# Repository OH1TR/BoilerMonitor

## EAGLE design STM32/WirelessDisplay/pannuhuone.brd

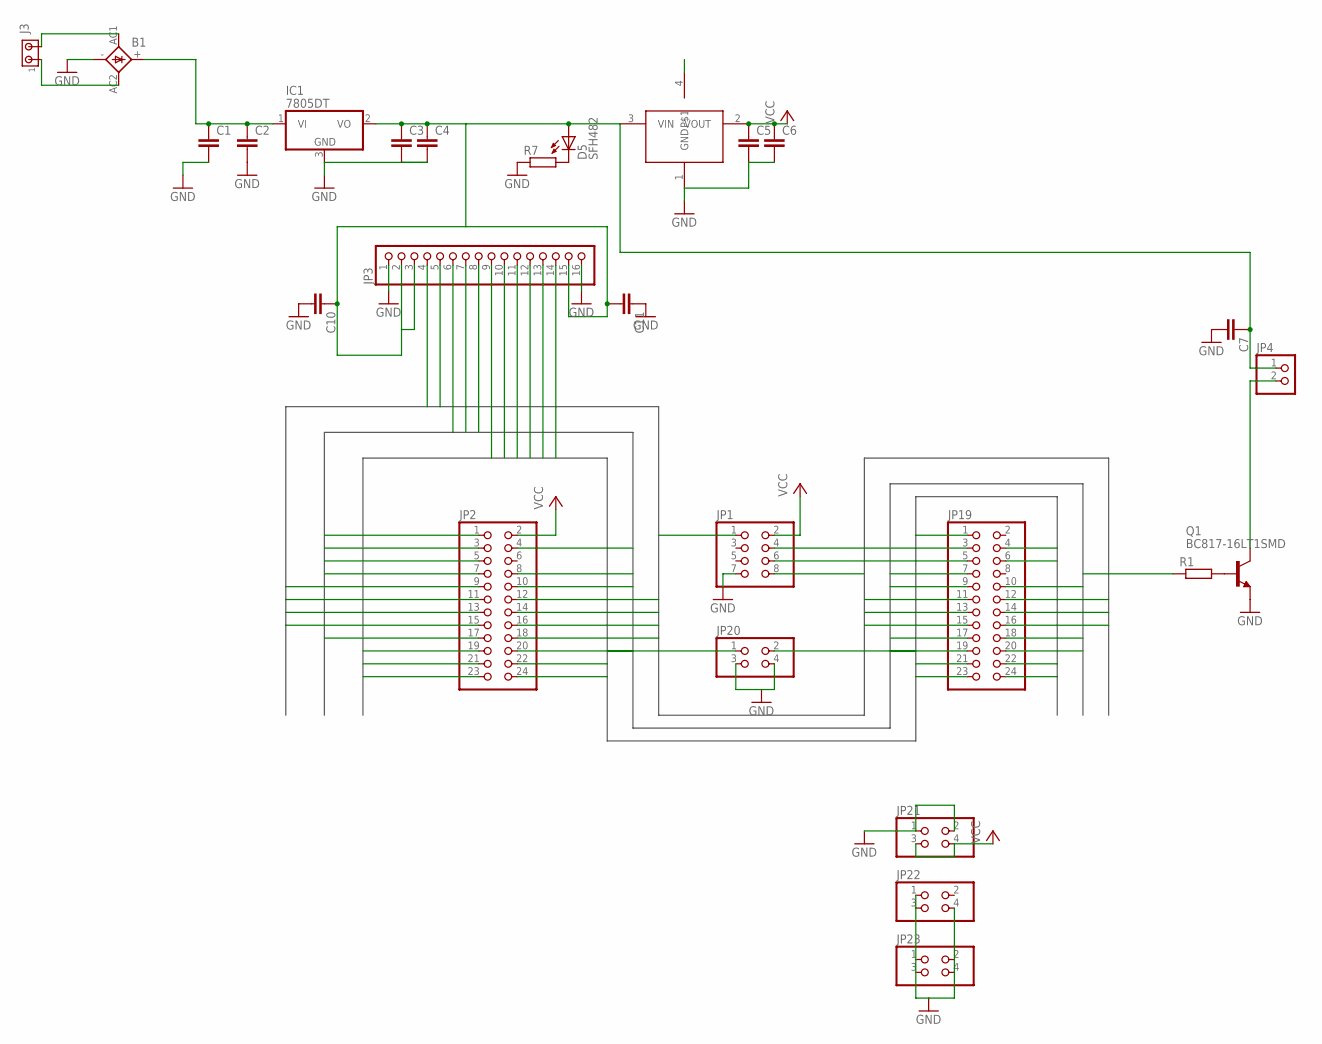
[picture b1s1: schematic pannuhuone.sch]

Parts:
B1: 2KBB-R
C1: C-EU025-050X050; C025-050X050
C2, C3, C4, C5, C6, C7, C10, C11: C-EUC1206; C1206
D5: SFH482
IC1: 7805DT; TO252
J3: MTA02-156; 1X2MTA
JP1: PINHD-2X4; 2X04
JP2, JP19: PINHD-2X12; 2X12
JP3: PINHD-1X16; 1X16
JP4: PINHD-1X2; 1X02
JP20, JP21, JP22, JP23: PINHD-2X2; 2X02
Q1: BC817-16LT1SMD; SOT23-BEC
R1, R7: R-EU_R1206; R1206
U$2: LD1117; SOT223

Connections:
GND: B1.-, C1.2, C2.2, C3.2, C4.2, C5.2, C6.2, C7.2, C10.2, C11.1, IC1.3 (GND), JP1.7, JP3.1, JP3.16, JP20.3, JP20.4, JP21.1, JP21.2, JP22.1, JP22.3, JP22.4, JP23.1, JP23.2, JP23.3, JP23.4, Q1.E, R7.1, U$2.1 (GND)
unnamed: B1.AC2, J3.1
unnamed: C3.1, C4.1, C7.1, C10.1, C11.2, D5.A, IC1.2 (VO), JP3.2, JP3.3, JP3.15, JP4.1, U$2.3 (VIN)
unnamed: D5.K (C), R7.2
unnamed: B1.AC1, J3.2
unnamed: Q1.B, R1.2
unnamed: JP4.2, Q1.C
unnamed: B1.+, C1.1, C2.1, IC1.1 (VI)
P$1: U$2.4
SPA0: JP2.9
SPA1: JP2.12
SPA2: JP1.1, JP2.11
SPA3: JP1.8, JP2.14
SPA4: JP2.13
SPA5: JP2.16
SPA6: JP2.15
SPA7: JP2.18
SPA8: JP19.16
SPA9: JP19.15
SPA10: JP19.14
SPA13: JP19.13
SPA14: JP3.4, JP19.11
SPA15: JP3.5, JP19.12
SPB0: JP1.4, JP2.19
SPB1: JP2.22
SPB2: JP2.21
SPB3: JP3.9, JP19.5
SPB4: JP3.10, JP19.6
SPB5: JP19.3
SPB6: JP3.11, JP19.4
SPB7: JP3.12, JP19.1
SPB8: JP3.13, JP20.2
SPB9: JP3.14, JP20.1
SPB10: JP2.24
SPB11: JP1.6, JP2.23
SPB12: JP19.24
SPB13: JP19.23
SPB14: JP19.22
SPB15: JP19.21
SPC0: JP2.5
SPC1: JP2.8
SPC2: JP2.7
SPC3: JP2.10
SPC4: JP2.17
SPC5: JP2.20
SPC6: JP19.20
SPC7: JP19.19, R1.1
SPC8: JP19.18
SPC9: JP19.17
SPC10: JP3.6, JP19.9
SPC11: JP3.7, JP19.10
SPC12: JP3.8, JP19.7
SPC13: JP2.1
SPC14: JP2.4
SPC15: JP2.3
VCC: C5.1, C6.1, JP1.2, JP2.2, JP21.3, JP21.4, U$2.2 (VOUT)

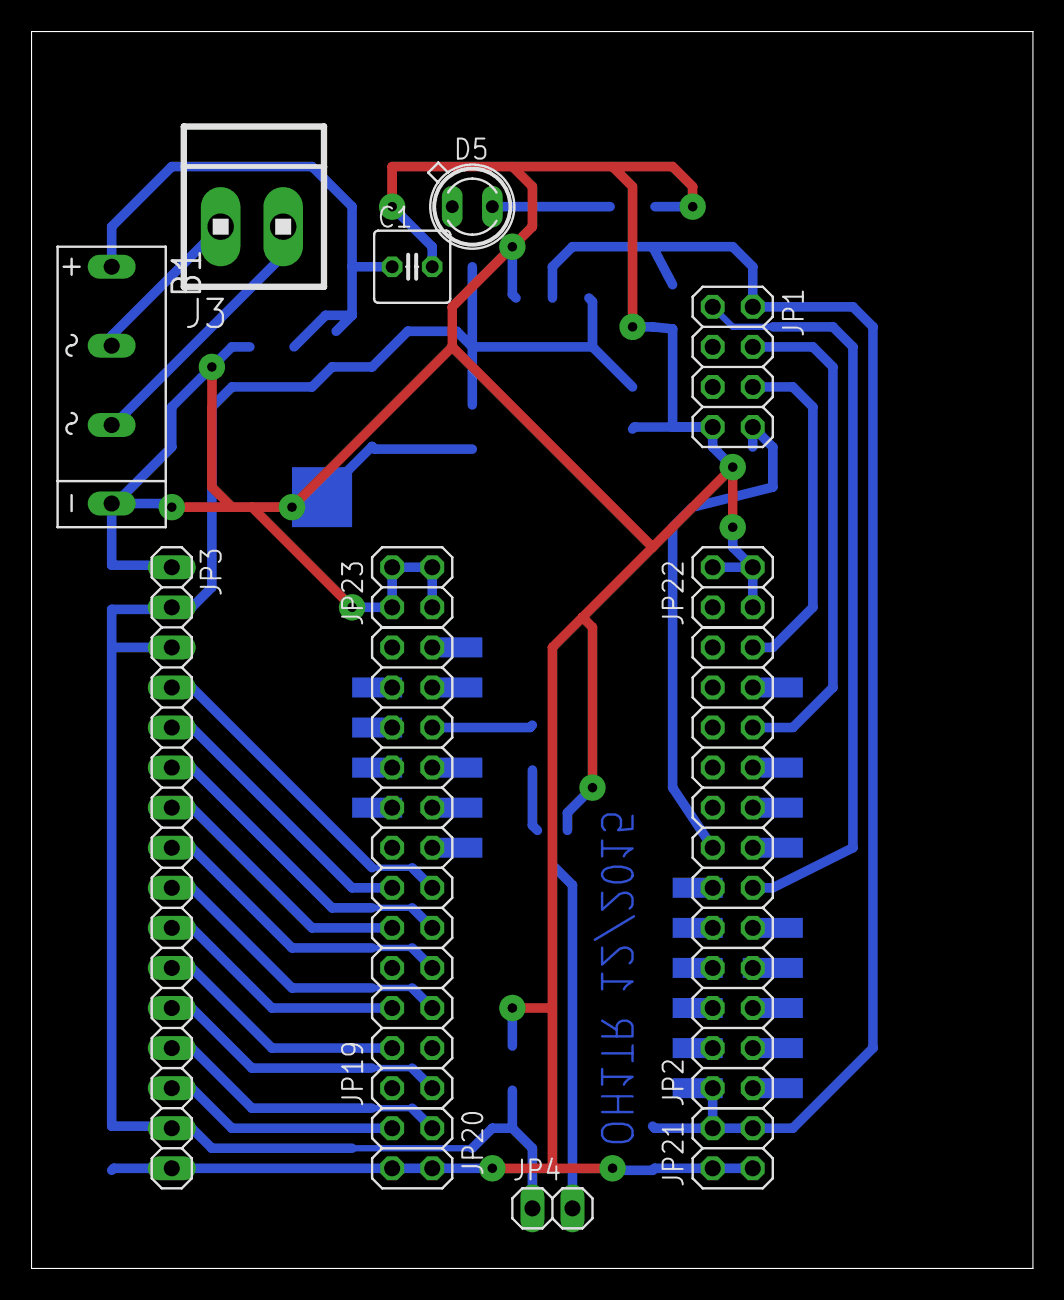
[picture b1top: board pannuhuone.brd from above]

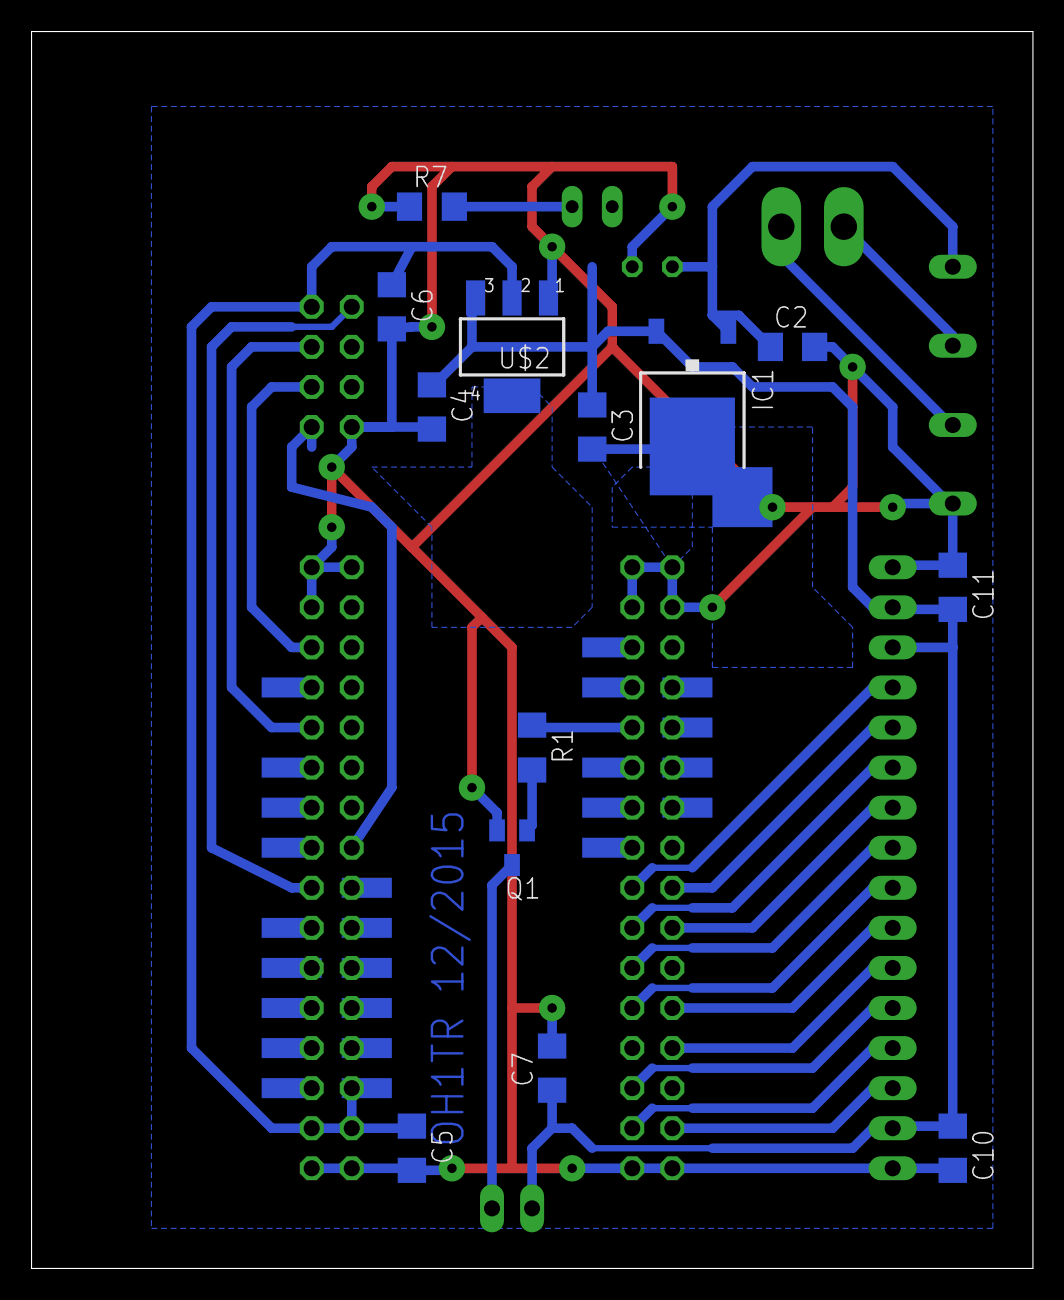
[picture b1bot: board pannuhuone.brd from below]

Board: 2 copper layers, 63.5 x 78.4 mm, 26 parts (13 on the bottom side), 25 nets.

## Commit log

2017-11-18 Initial commit.
2017-11-22 First working version.
2019-11-23 Added STM32 board and code.
2019-11-23 Bump Microsoft.AspNetCore.All in /BoilerMonitorServer
    Bumps [Microsoft.AspNetCore.All](https://github.com/aspnet/Universe) from 2.0.0 to 2.0.9.
    - [Release notes](https://github.com/aspnet/Universe/releases)
    - [Changelog](https://github.com/aspnet/Universe/blob/master/docs/CrossRepoBreakingChanges.md)
    - [Commits](https://github.com/aspnet/Universe/compare/2.0.0...2.0.9)
2021-04-25 Test publish
2021-04-25 Project selection
2021-04-25 Add or update the Azure App Service build and deployment workflow config
2021-04-25 Remove the Azure App Service build and deployment workflow config
2021-04-25 Add or update the App Service deployment workflow configuration from Azure Portal.
2021-04-25 Testing
2021-06-12 Accept multiple values
2021-06-12 test
2021-06-20 Added DataLoader
2021-06-21 Added Xamarin App
2021-06-21 Separated server and app solutions.
